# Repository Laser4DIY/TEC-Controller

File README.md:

# Laser4DIY TEC Controller

This is the repository for the TEC (ThermoElectric Cooling) controller used in the [Laser4DIY project](http://www.laser4diy.org/).

## Specs

* Designed as a shield for the Arduino Due
* 2-channel TEC controller, driving peltier elements up to 106W heat transfer capacity per channel (12A at 15.5V)
* 2 boards can be stacked for a 4-channel TEC controller, driven by a single Arduino Due

## Repository Layout

```
+ Firmware                      firmware directory
| + Firmware.ino                Main Arduino firmware source code file
| + functions_PWM_DAC.ino       source code
| + LICENSE.txt                 license for the fimware
| + main_loop.ino               source code
| + main_setup.ino              source code
+ Hardware                      hardware directory
| + cern_ohl_v_1_2_howto.pdf    Howto for the used hardware license
| + CHANGES.txt                 list of hardware changes
| + finalboard.jpg              photo of the final board
| + LICENSE.txt                 license for the hardware
| + README.txt                  hardware readme
| + schematic.png               schematic
| + TEC-Controller.brd          board layout
| + TEC-Controller.sch          schematic
```

## Documentation

The TEC Controller is documented at [FabLab München Wiki](https://wiki.fablab-muenchen.de/display/WIKI/LASER4DIY+-+TEC+Controller).

## Known Issues

See [Open Issues](https://github.com/Laser4DIY/TEC-Controller/issues?utf8=%E2%9C%93&q=is%3Aopen+is%3Aissue).

## License

The hardware documentation is licensed under CERN OHL v.1.2.

The firmware is licensed under GPLv3.

For details see licensing info in the respective sub directories.

---

Copyright FabLab München e.V. 2018

Laser4DIY is sponsored by the Federal Ministry of Education and Research

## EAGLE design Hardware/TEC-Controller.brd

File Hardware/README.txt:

Copyright FabLab Muenchen e.V. 2018.

This documentation describes Open Hardware and is licensed under the CERN OHL v. 1.2.

You may redistribute and modify this documentation under the terms of the CERN OHL v.1.2. 
(http://ohwr.org/cernohl). This documentation is distributed WITHOUT ANY EXPRESS OR 
IMPLIED WARRANTY, INCLUDING OF MERCHANTABILITY, SATISFACTORY QUALITY AND FITNESS FOR A 
PARTICULAR PURPOSE. 

Please see the CERN OHL v.1.2 for applicable conditions.

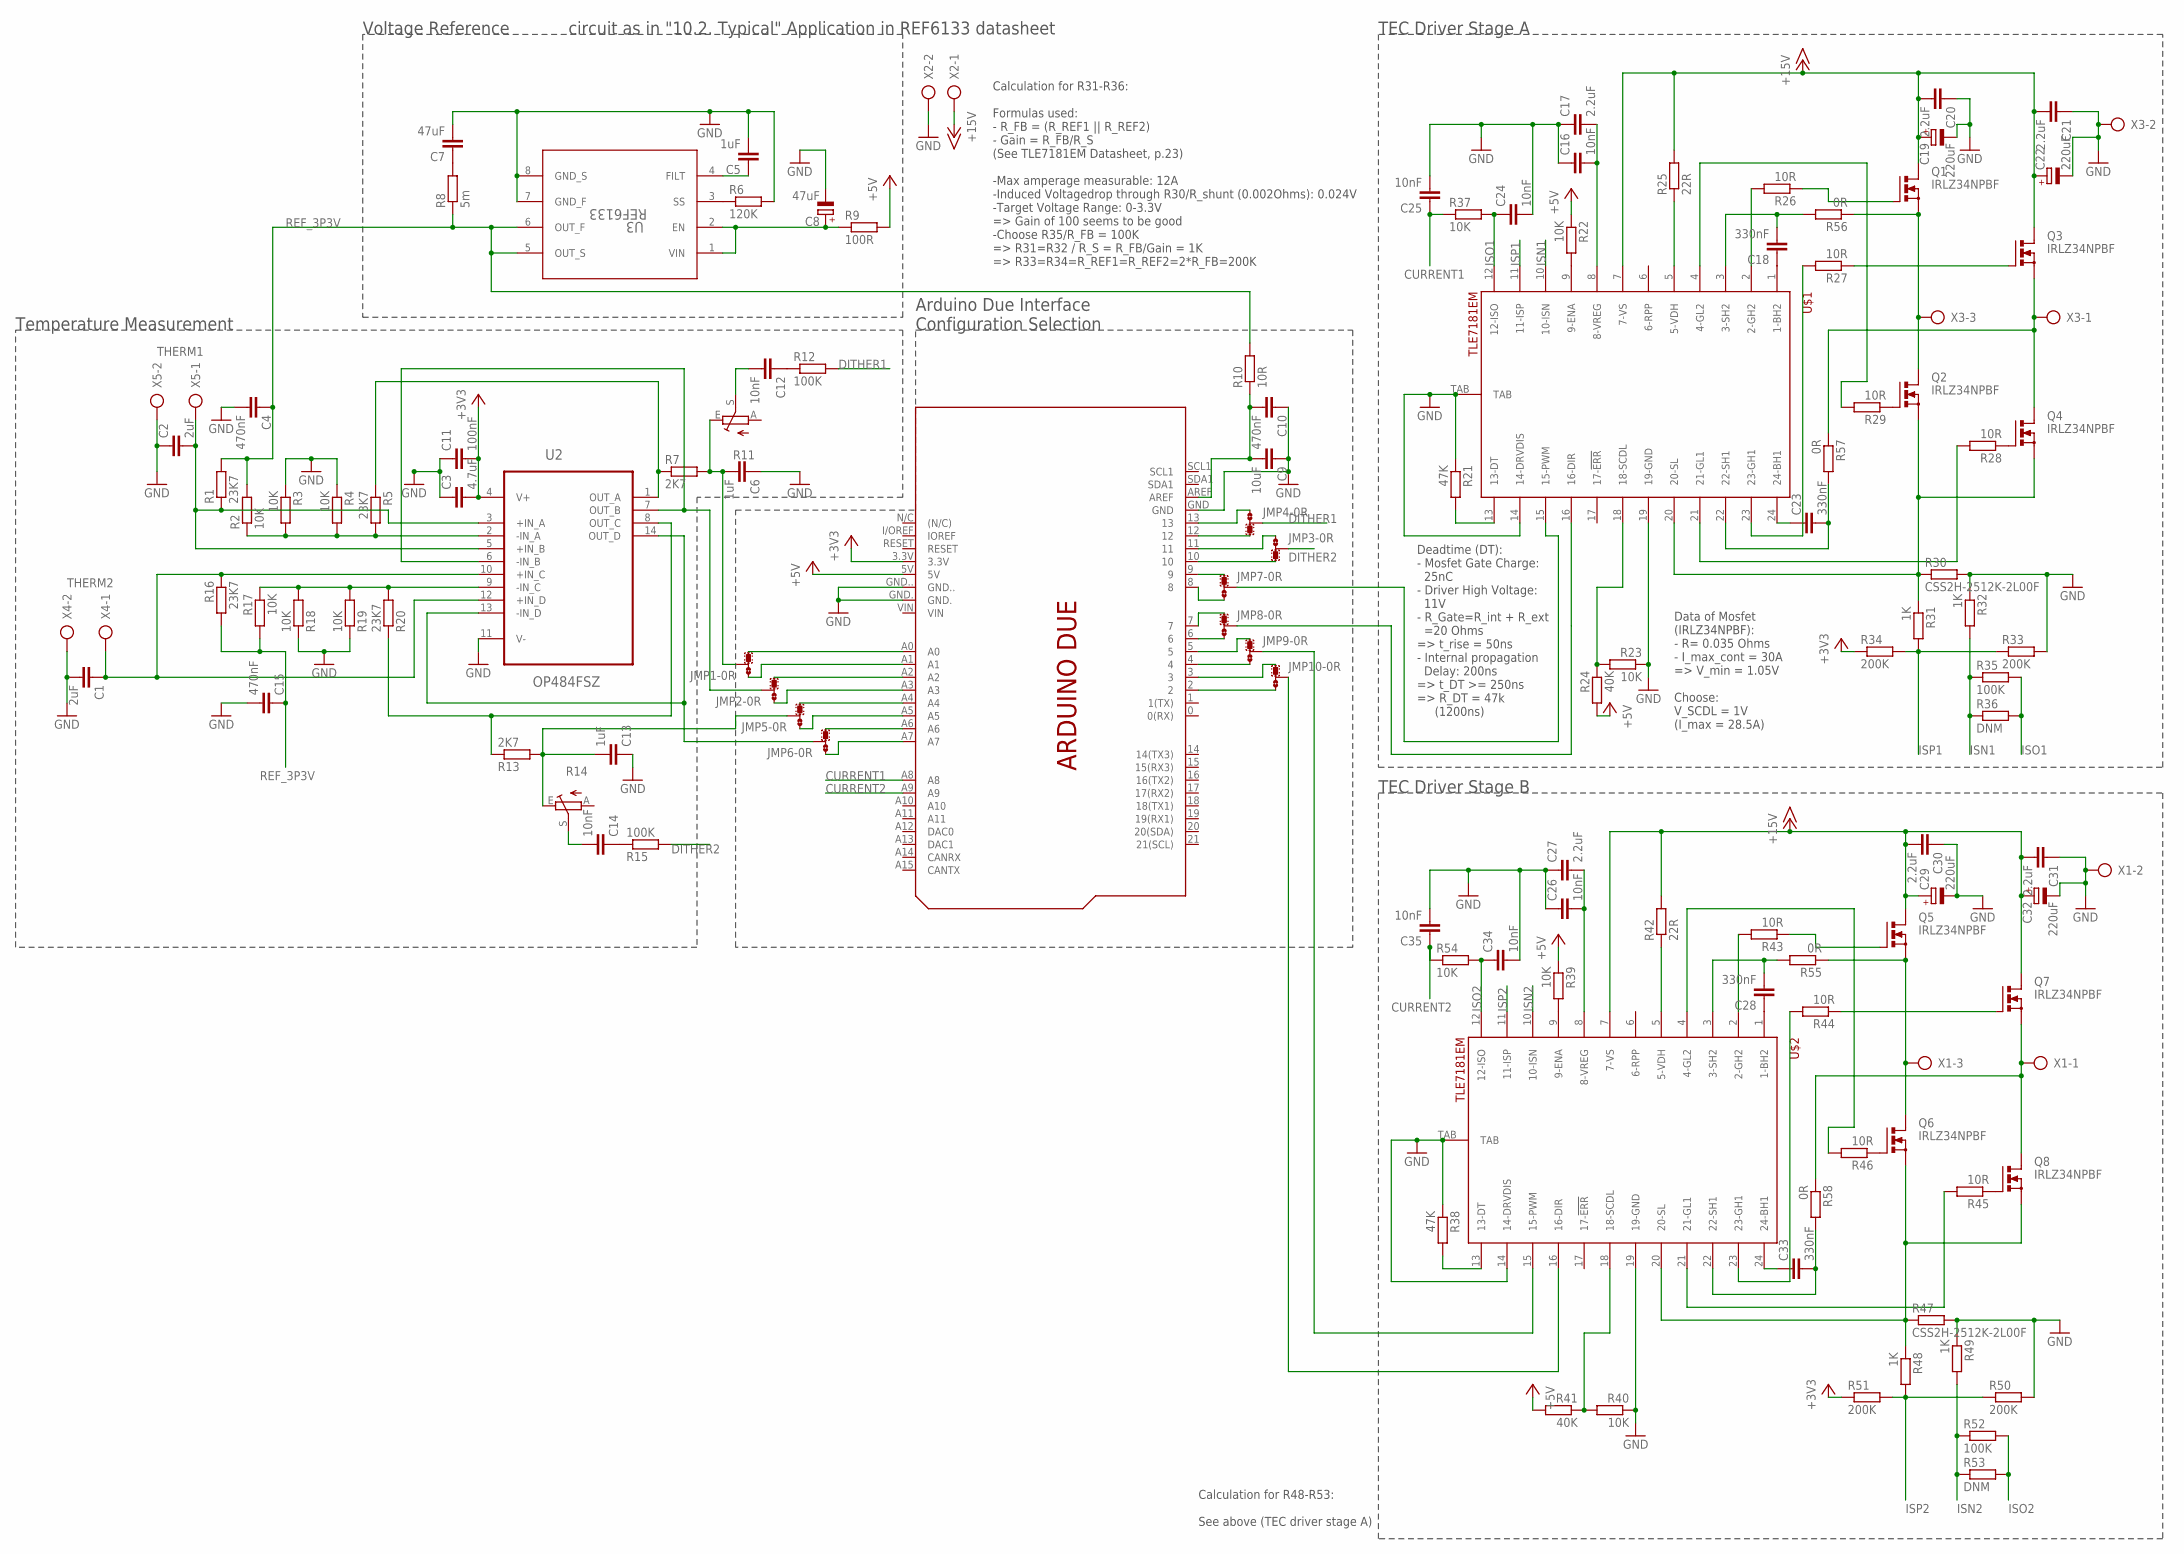
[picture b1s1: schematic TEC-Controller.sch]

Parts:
C1, C2: 2uF; C0805
C3: 4.7uF; C0603
C4: 470nF; C0805
C5, C6, C13: 1uF; C0805
C7: 47uF; C0603
C8: 47uF; PANASONIC_D
C9: 10uF; C0603
C10, C15: 470nF; C0603
C11: 100nF; C0603
C12, C14: 10nF; C0805
C16, C24, C25: 10nF; C0603K
C17, C20, C21, C30, C31: 2.2uF; C0603K
C18, C23, C28, C33: 330nF; C0603K
C19, C22, C29, C32: 220uF; E2,5-7
C26, C34, C35: 10nF; C0603
C27: 2.2uF; C0603
JMP1, JMP2, JMP3, JMP4, JMP5, JMP6, JMP7, JMP8, JMP9, JMP10: 0R-JUMPA; A0R-JMP
PCB1: ARDUINO_DUE_SHIELD
Q1, Q2, Q3, Q4, Q5, Q6, Q7, Q8: IRLZ34NPBF; TO220BV
R1: 23K7; R0603
R2, R3, R22, R23, R37, R39, R40, R54: 10K; R0603
R4, R17, R18, R19: 10K; R0805
R5, R16, R20: 23K7; R0805
R6: 120K; R0805
R7, R13: 2K7; R0805
R8: 5m; R0603
R9: 100R; R0805
R10, R26: 10R; R0805
R11, R14: TRIM_EU-B64W; B64W
R12, R15: 100K; R0805
R21, R38: 47K; R0603
R24, R41: 40K; R0603
R25, R42: 22R; R0603
R27, R28, R29, R43, R44, R45, R46: 10R; 0204/7
R30, R47: CSS2H-2512K-2L00F; R2512
R31, R32, R48, R49: 1K; R0603
R33, R34, R50, R51: 200K; R0603
R35, R52: 100K; R0603
R36, R53: DNM; R0603
R55, R56, R57, R58: 0R; 0204/7
U2: OP484FSZ; SOIC127P600X175-14N
U3: REF6133; DGK0008A_N
U$1, U$2: TLE7181EM; PG-SSOP-24-4
X1, X3: AK500/3
X2, X4, X5: AK500/2

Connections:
+3V3: C3.2, C11.2, PCB1.3.3V, R34.1, R51.1, U2.4 (V+)
+5V: PCB1.5V, R9.2, R22.1, R24.2, R39.1, R41.2
+15V: C19.+, C20.2, C21.2, C22.+, C29.+, C30.2, C31.2, C32.+, Q1.D, Q3.D, Q5.D, Q7.D, R25.2, R42.2, U$1.7 (7-VS), U$2.7 (7-VS), X2.1
CURRENT1: C25.1, PCB1.A8, R37.1
CURRENT2: C35.1, PCB1.A9, R54.1
DITHER1: JMP4.2, R12.2
DITHER2: JMP3.2, R15.2
GND: C1.2, C2.1, C3.1, C4.2, C5.2, C6.1, C7.2, C8.-, C9.1, C10.1, C11.1, C13.1, C15.2, C16.1, C17.1, C19.-, C20.1, C21.1, C22.-, C24.2, C25.2, C26.1, C27.1, C29.-, C30.1, C31.1, C32.-, C34.2, C35.2, PCB1.GND, PCB1.GND., PCB1.GND.., R3.1, R4.1, R6.2, R18.1, R19.1, R21.1, R23.1, R30.2, R32.1, R33.2, R38.1, R40.1, R47.2, R49.1, R50.2, U2.11 (V-), U3.7 (GND_F), U3.8 (GND_S), U$1.14 (14-DRVDIS), U$1.19 (19-GND), U$1.TAB, U$2.14 (14-DRVDIS), U$2.19 (19-GND), U$2.TAB, X1.2, X2.2, X3.2, X4.2, X5.2
ISN1: R32.2, R35.1, R36.1, U$1.10 (10-ISN)
ISN2: R49.2, R52.1, R53.1, U$2.10 (10-ISN)
ISO1: C24.1, R35.2, R36.2, R37.2, U$1.12 (12-ISO)
ISO2: C34.1, R52.2, R53.2, R54.2, U$2.12 (12-ISO)
ISP1: R31.2, R33.1, R34.2, U$1.11 (11-ISP)
ISP2: R48.2, R50.1, R51.2, U$2.11 (11-ISP)
unnamed: C28.2, R55.2, U$2.3 (3-SH2)
unnamed: C2.2, R1.1, U2.3 (+IN_A), U2.5 (+IN_B), X5.1
unnamed: C1.1, R16.1, U2.10 (+IN_C), U2.12 (+IN_D), X4.1
unnamed: R2.1, R3.2, R4.2, R5.2, U2.2 (-IN_A)
unnamed: C18.2, R56.2, U$1.3 (3-SH2)
unnamed: JMP2.2, U2.6 (-IN_B), U2.7 (OUT_B)
unnamed: R5.1, R7.1, U2.1 (OUT_A)
unnamed: JMP4.3, PCB1.12
unnamed: JMP1.3, PCB1.A0
unnamed: C5.1, U3.4 (FILT)
unnamed: R6.1, U3.3 (SS)
unnamed: JMP1.1, PCB1.A1
unnamed: JMP2.3, PCB1.A2
unnamed: C6.2, JMP1.2, R7.2, R11.E
unnamed: JMP2.1, PCB1.A3
unnamed: C7.1, R8.2
unnamed: C8.+, R9.1, U3.1 (VIN), U3.2 (EN)
unnamed: C9.2, C10.2, PCB1.AREF, R10.1
unnamed: C12.2, R11.S
unnamed: JMP3.1, PCB1.11
unnamed: JMP4.1, PCB1.13
unnamed: JMP7.1, PCB1.9
unnamed: JMP3.3, PCB1.10
unnamed: C12.1, R12.1
unnamed: R17.1, R18.2, R19.2, R20.2, U2.9 (-IN_C)
unnamed: R13.1, R20.1, U2.8 (OUT_C)
unnamed: C13.2, JMP5.2, R13.2, R14.E
unnamed: C14.1, R15.1
unnamed: C14.2, R14.S
unnamed: JMP5.3, PCB1.A4
unnamed: JMP5.1, PCB1.A5
unnamed: JMP7.3, PCB1.8
unnamed: JMP6.3, PCB1.A6
unnamed: JMP6.1, PCB1.A7
unnamed: JMP6.2, U2.13 (-IN_D), U2.14 (OUT_D)
unnamed: JMP8.1, PCB1.7
unnamed: JMP8.3, PCB1.6
unnamed: JMP7.2, U$1.15 (15-PWM)
unnamed: JMP8.2, U$1.16 (16-DIR)
unnamed: R21.2, U$1.13 (13-DT)
unnamed: R23.2, R24.1, U$1.18 (18-SCDL)
unnamed: R22.2, U$1.9 (9-ENA)
unnamed: R25.1, U$1.5 (5-VDH)
unnamed: C16.2, C17.2, U$1.8 (8-VREG)
unnamed: R26.2, U$1.2 (2-GH2)
unnamed: Q1.G, R26.1
unnamed: Q1.S, Q2.D, R56.1, X3.3
unnamed: C18.1, U$1.1 (1-BH2)
unnamed: R27.2, U$1.23 (23-GH1)
unnamed: Q3.G, R27.1
unnamed: Q3.S, Q4.D, R57.1, X3.1
unnamed: C23.1, U$1.24 (24-BH1)
unnamed: Q4.G, R28.1
unnamed: Q2.G, R29.1
unnamed: R29.2, U$1.4 (4-GL2)
unnamed: R28.2, U$1.21 (21-GL1)
unnamed: Q2.S, Q4.S, R30.1, R31.1, U$1.20 (20-SL)
unnamed: JMP9.2, U$2.15 (15-PWM)
unnamed: C33.2, R58.2, U$2.22 (22-SH1)
unnamed: JMP10.2, U$2.16 (16-DIR)
unnamed: R38.2, U$2.13 (13-DT)
unnamed: R39.2, U$2.9 (9-ENA)
unnamed: R40.2, R41.1, U$2.18 (18-SCDL)
unnamed: C26.2, C27.2, U$2.8 (8-VREG)
unnamed: R42.1, U$2.5 (5-VDH)
unnamed: R43.2, U$2.2 (2-GH2)
unnamed: Q5.S, Q6.D, R55.1, X1.3
unnamed: C28.1, U$2.1 (1-BH2)
unnamed: Q5.G, R43.1
unnamed: R44.2, U$2.23 (23-GH1)
unnamed: Q7.G, R44.1
unnamed: Q7.S, Q8.D, R58.1, X1.1
unnamed: C33.1, U$2.24 (24-BH1)
unnamed: Q8.G, R45.1
unnamed: Q6.G, R46.1
unnamed: R46.2, U$2.4 (4-GL2)
unnamed: R45.2, U$2.21 (21-GL1)
unnamed: Q6.S, Q8.S, R47.1, R48.1, U$2.20 (20-SL)
unnamed: C23.2, R57.2, U$1.22 (22-SH1)
unnamed: JMP9.1, PCB1.5
unnamed: JMP9.3, PCB1.4
unnamed: JMP10.1, PCB1.3
unnamed: JMP10.3, PCB1.2
REF_3P3V: C4.1, C15.1, R1.2, R2.2, R8.1, R10.2, R16.2, R17.2, U3.5 (OUT_S), U3.6 (OUT_F)

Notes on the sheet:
THERM1
THERM2
Voltage Reference
Temperature Measurement
Arduino Due Interface Configuration Selection
TEC Driver Stage A
TEC Driver Stage B
circuit as in "10.2. Typical" Application in REF6133 datasheet
Calculation for R31-R36: Formulas used: - R_FB = (R_REF1 || R_REF2) - Gain = R_FB/R_S (See TLE7181EM Datasheet, p.23) -Max amperage measurable: 12A -Induced Voltagedrop through R30/R_shunt (0.002Ohms): 0.024V -Target Voltage Range: 0-3.3V => Gain of 100 seems to be good -Choose R35/R_FB = 100K => R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
Calculation for R48-R53: See above (TEC driver stage A)
Data of Mosfet (IRLZ34NPBF): - R= 0.035 Ohms - I_max_cont = 30A => V_min = 1.05V Choose: V_SCDL = 1V (I_max = 28.5A)
Deadtime (DT): - Mosfet Gate Charge: 25nC - Driver High Voltage: 11V - R_Gate=R_int + R_ext =20 Ohms => t_rise = 50ns - Internal propagation Delay: 200ns => t_DT >= 250ns => R_DT = 47k (1200ns)

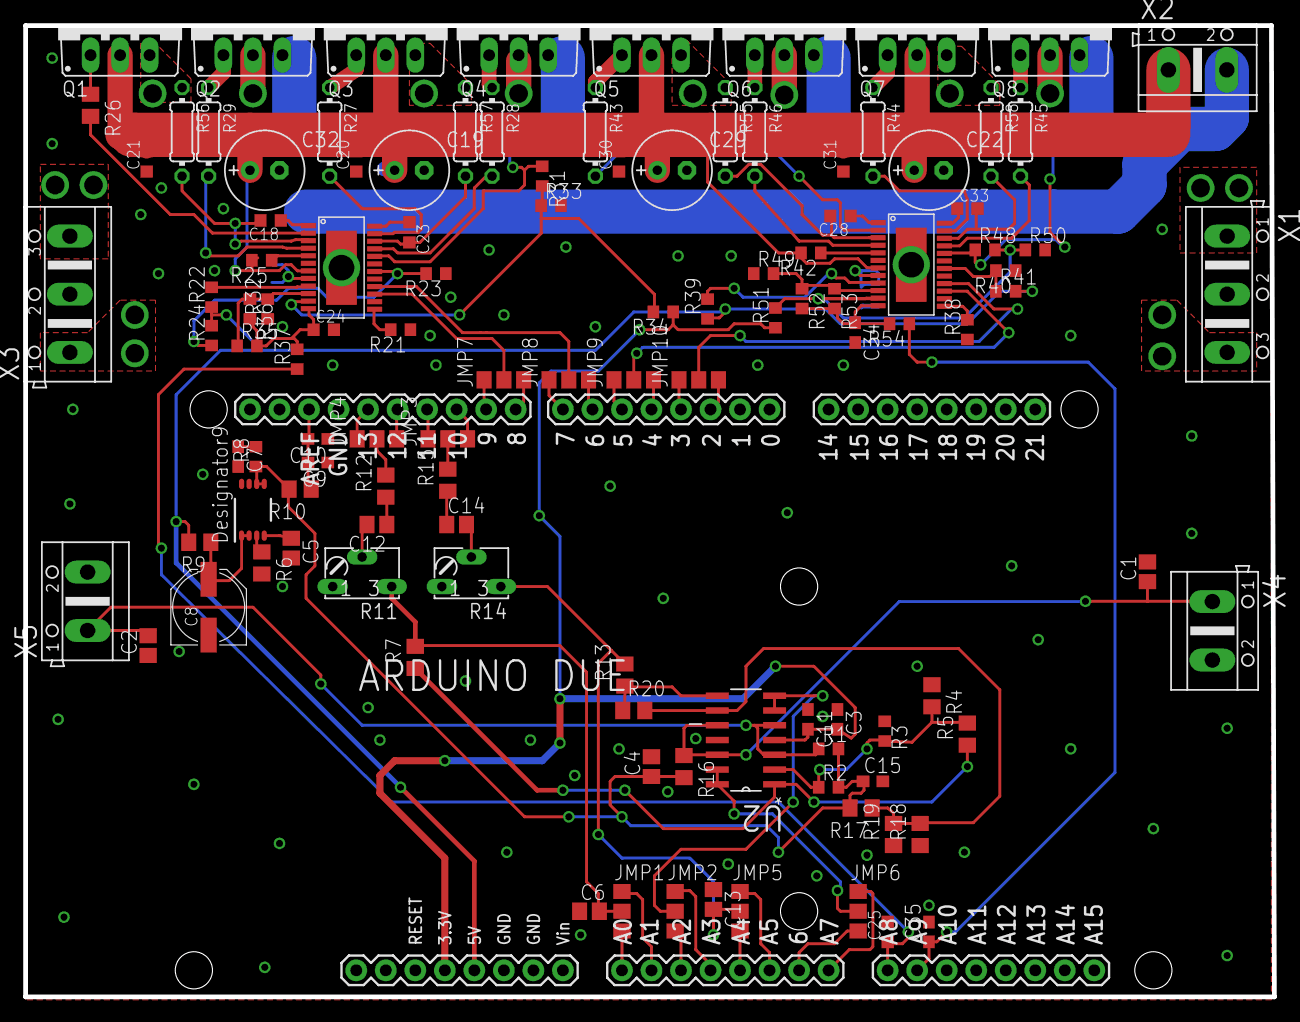
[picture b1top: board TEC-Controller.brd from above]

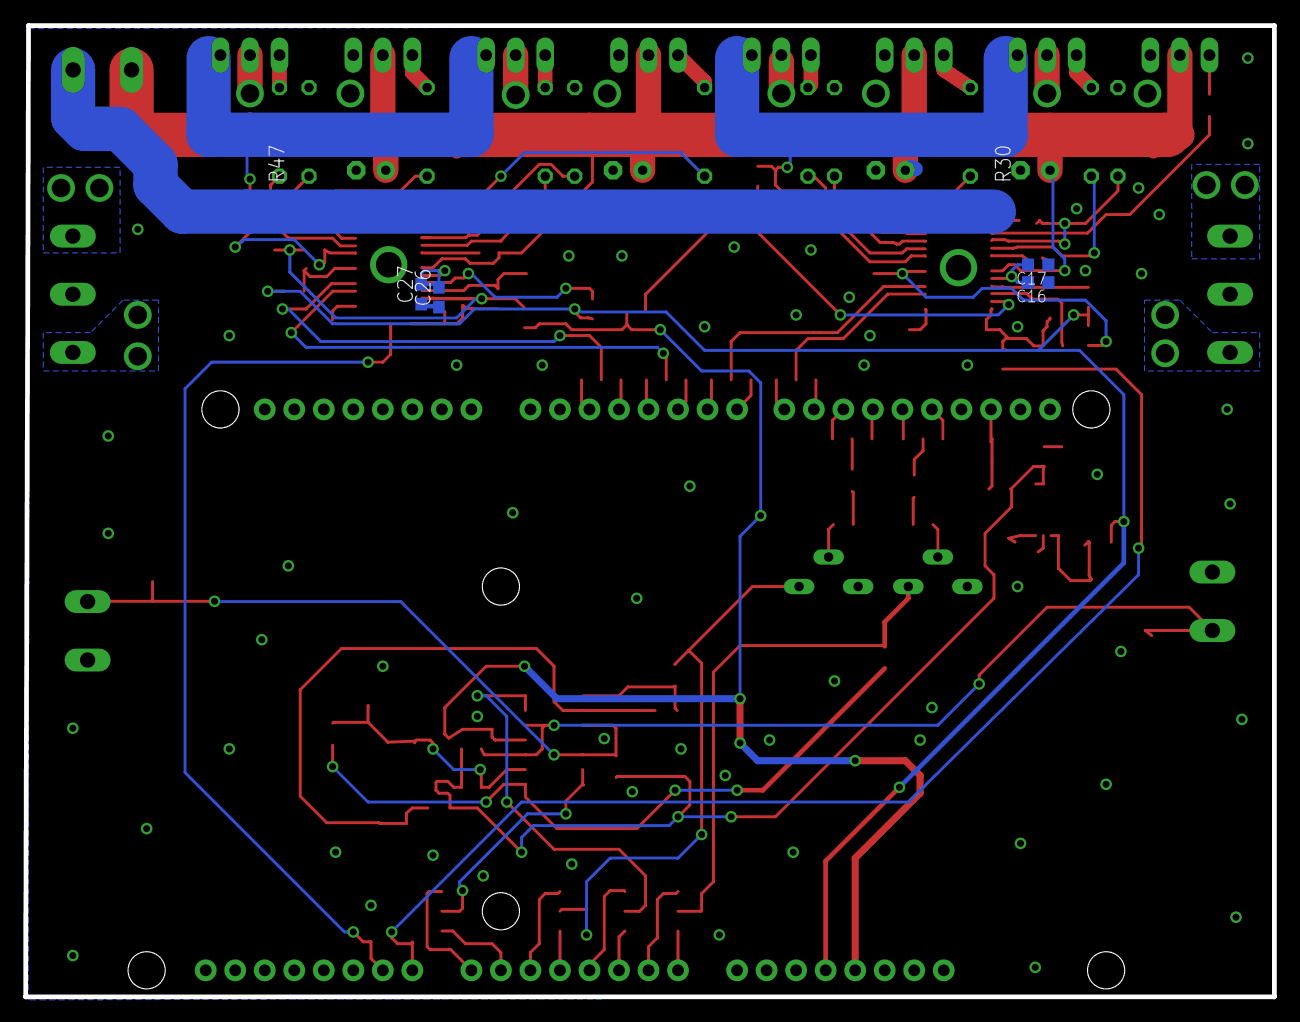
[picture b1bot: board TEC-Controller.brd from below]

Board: 2 copper layers, 107.4 x 83.6 mm, 121 parts (6 on the bottom side), 98 nets.

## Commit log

2018-03-29 initial commit
    This is a testversion
2018-11-09 added licensing info
2018-11-10 added schematic as png
2018-11-10 Added CERN OHL howto and changes.txt
2018-11-10 renamed main ino file to match folder name
2018-11-10 added readme.md
2018-11-10 fixed image link
2018-11-10 Added link to open issues
